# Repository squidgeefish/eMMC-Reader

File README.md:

# eMMC-Reader
A GL3224-based eMMC reader

## Why?

The Sabrent USB readers that had this chip were recently (2022?) updated to use the 48-QFN version with dual LUNs. This happened to break the single-bit eMMC mode, and that makes me very sad. Rather than trawling eBay for NOS packaging, I figured I should just make a better tool.

This also includes a TXS02612 that is being used as a 1.8V level shifter like on an Exploitee.rs [Low Voltage eMMC Adapter](https://shop.exploitee.rs/shop/p/low-voltage-emmc-adapter) because those are great.\
Note that this is a mux, which isn't necessary in this application. I could wire it up to an SD card socket, but that's overkill. According to [TI's Product Overview for SDIO voltage translators](https://www.ti.com/lit/an/scea096/scea096.pdf), the TXS0206 is a non-mux version of this, but it only supports 60Mbps (as opposed to 120Mbps) and is a WCSP. I've gotten more than 60Mbps out of an exploitee.rs board in single-bit mode, so I'm going to stick with the proven chip.

#### Why not USB-C?
Because I don't trust you not to break it...

The GL3224 supports USB 3.0 (5Gbps). To implement that with a USB-C connector, there are two options:
1. Use a plug and hook up one pair of `SS[R,T]X` lines as well as a 5K1 pulldown on CC1. The computer into which this is plugged will have to figure out which pair is live.
2. Use a receptacle and include a SuperSpeed-capable mux like an `HD3SS3220` since you can't trust a user to plug the cable in the "right" way.

USB-C plugs suck because they need thin PCBs and you will break one off in your computer at some point. Unless you use a (technically illegal) extension cable, and then we're back to the same impasse as we had with the receptacle in the first place. It's easier and more robust to use a USB 3.0 Type-A connector (I typically wind up using the Sabrent USB reader with a USB 2.0 extension cable anyway to keep the clock speeds down).

## Links

- [Somebody who reversed a GL3224 adapter](https://www.801labs.org/research-portal/post/reverse-engineering-4-layer-pcb/)
- [Sample (reverse-engineered as above) schematic](https://github.com/dvdfreitag/USB3-eMMC)
- [Eagle Library for the 48- and 32-QFN parts](https://github.com/dvdfreitag/eagle_libraries/blob/bc423563c25ef42febea000f4a0536ccb97d0efd/GenesysLogic.lbr)

Note that this schematic is a little more grand than the bare minimum necessary; the Sabrent reader that inspired this project doesn't bother with the external oscillator.

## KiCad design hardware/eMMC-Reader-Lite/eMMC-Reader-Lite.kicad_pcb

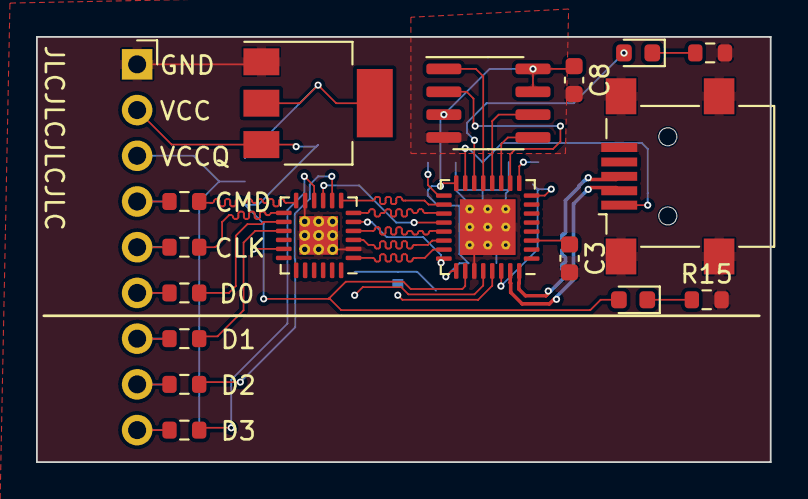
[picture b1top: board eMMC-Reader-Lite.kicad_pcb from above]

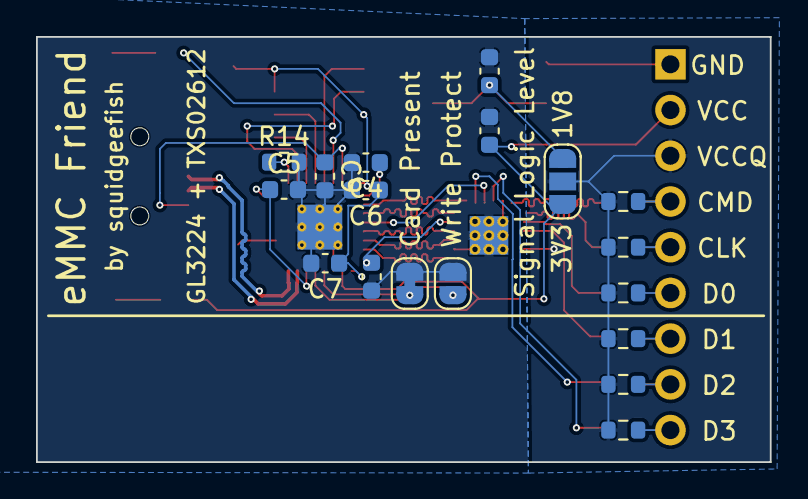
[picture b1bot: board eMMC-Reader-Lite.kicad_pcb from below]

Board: 2 copper layers, 40.8 x 23.6 mm, 36 parts (18 on the bottom side), 40 nets.

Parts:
C1, C3, C6, C7, C8: 0.1uF; C_0603_1608Metric
C4, C5: 1uF; C_0603_1608Metric
C9: 2.2uF; C_0603_1608Metric
C10, C11: 4.7uF; C_0603_1608Metric
D1, D2: LED_Small_Filled; LED_0603_1608Metric
J1: Conn_01x09_Socket; PinSocket_1x09_P2.54mm_Horizontal
J2: USB_B_Mini; USB_Mini-B_Lumberg_2486_01_Horizontal
JP1: SolderJumper_2_Open; SolderJumper-2_P1.3mm_Open_RoundedPad1.0x1.5mm
JP2: SolderJumper_2_Bridged; SolderJumper-2_P1.3mm_Bridged_RoundedPad1.0x1.5mm
JP3: SolderJumper_3_Open; SolderJumper-3_P1.3mm_Open_RoundedPad1.0x1.5mm
R1, R2, R3, R4, R5, R6: 0; R_0603_1608Metric
R7, R8, R9, R10, R11, R12: 47; R_0603_1608Metric
R13, R15: 220; R_0603_1608Metric
R14: 680; R_0603_1608Metric
U1: QFN-32-1EP_5x5mm_P0.5mm_EP3.1x3.1mm_ThermalVias
U2: TXS02612; QFN-24-1EP_4x4mm_P0.5mm_EP2.15x2.15mm_ThermalVias
U3: W25X20CLSN; SOIC-8_3.9x4.9mm_P1.27mm
U4: LM1117MP-1.8; SOT-223-3_TabPin2

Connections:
+1V8: C11.1, JP3.1 (A), U4.2 (VO)
+3V3: C6.1, C7.1, C8.1, U1.16 (DVDD33), U1.25 (DVDD33), U3.3 (~WP), U3.7 (~HOLD), U3.8 (VCC)
/D+: J2.3 (D+), U1.32 (D+)
/D-: J2.2 (D-), U1.31 (D-)
/SD_CD#: JP2.1 (A), U1.29 (SD_CDZ)
/SD_VCC: C10.1, D2.2 (A), J1.2, JP3.3 (B), U1.26 (SD_VCC), U4.3 (VI)
/SD_WP: JP1.1 (A), U1.28 (SD_WP)
/VCCA: C1.1, U1.24 (SD_VCCQ), U2.5 (VCCA), U2.24 (SEL)
GND: C1.2, C3.2, C4.2, C5.2, C6.2, C7.2, C8.2, C9.2, C10.2, C11.2, J1.1, J2.5 (GND), J2.6 (Shield), JP1.2 (B), JP2.2 (B), R13.2, R14.2, R15.2, U1.27 (GND), U1.33 (GND), U2.2 (GND), U2.11 (GND), U2.25 (GND), U3.4 (GND), U4.1 (GND)
unnamed: C5.1, U1.8 (AVDD33), U1.30 (AVDD33)
unnamed: D1.2 (A), U1.14 (LED)
unnamed: D1.1 (K), R13.1
unnamed: D2.1 (K), R15.1
unnamed: J1.4, R1.2, R12.1
unnamed: J1.5, R2.2, R11.1
unnamed: J1.6, R3.2, R10.1
unnamed: J1.7, R4.2, R9.1
unnamed: J1.8, R5.2, R8.1
unnamed: J1.9, R6.2, R7.1
unnamed: R14.1, U1.9 (RTERM)
unnamed: U1.20 (SD_CLK), U2.9 (CLKA)
unnamed: U1.21 (SD_CMD), U2.4 (CMDA)
unnamed: U1.19 (SD_D0), U2.6 (DAT0A)
unnamed: U1.18 (SD_D1), U2.7 (DAT1A)
unnamed: U1.23 (SD_D2), U2.1 (DAT2A)
unnamed: U1.22 (SD_D3), U2.3 (DAT3A)
unnamed: U1.12 (SPI_CK), U3.6 (SCK)
unnamed: U1.13 (SPI_CS), U3.1 (~CS)
unnamed: U1.10 (SPI_MISO), U3.2 (DO(IO1))
unnamed: U1.11 (SPI_MOSI), U3.5 (DI(IO0))
unnamed: C3.1, U1.3 (AVDD12)
unnamed: C4.1, U1.17 (DVDD12)
unnamed: R2.1, U2.13 (CLKB_1)
unnamed: R1.1, U2.12 (CMDB_1)
unnamed: R3.1, U2.14 (DAT0B_1)
unnamed: R4.1, U2.15 (DAT1B_1)
unnamed: R5.1, U2.8 (DAT2B_1)
unnamed: R6.1, U2.10 (DAT3B_1)
VBUS: C9.1, J2.1 (VBUS), U1.15 (VBUS)
VCCQ: J1.3, JP3.2 (C), R7.2, R8.2, R9.2, R10.2, R11.2, R12.2, U2.17 (VCCB_1)

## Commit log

2024-09-07 Add TXS02612 and GL3224 symbols
2024-09-07 Mostly done with schematic
2024-09-07 README musings
2024-09-07 Finish up schematic (added switches and regulators); just some power caps to go
2024-09-08 Finish schematic; partial layout for fully-featured board
2024-09-08 gitignore
2024-09-10 Make stripped-down 'eMMC Friend'-style schematic and layout
2024-09-11 Add yellow fill to symbols; add GL3224 pin 27 (GND)
2024-09-11 Further routing
    Need fills, GL3224 test points, length-matching from GL3224
    Might need more blinky
2024-09-11 whoops forgot the sym-lib-table
2024-09-11 Break out SD_VCC output rail to be distinct from 3V3 net
    Add indicator LED for that rail
2024-09-11 Fix swapped USB data lines
2024-09-11 Basic routing (needs properly-sized traces, cleaner copper pours)
